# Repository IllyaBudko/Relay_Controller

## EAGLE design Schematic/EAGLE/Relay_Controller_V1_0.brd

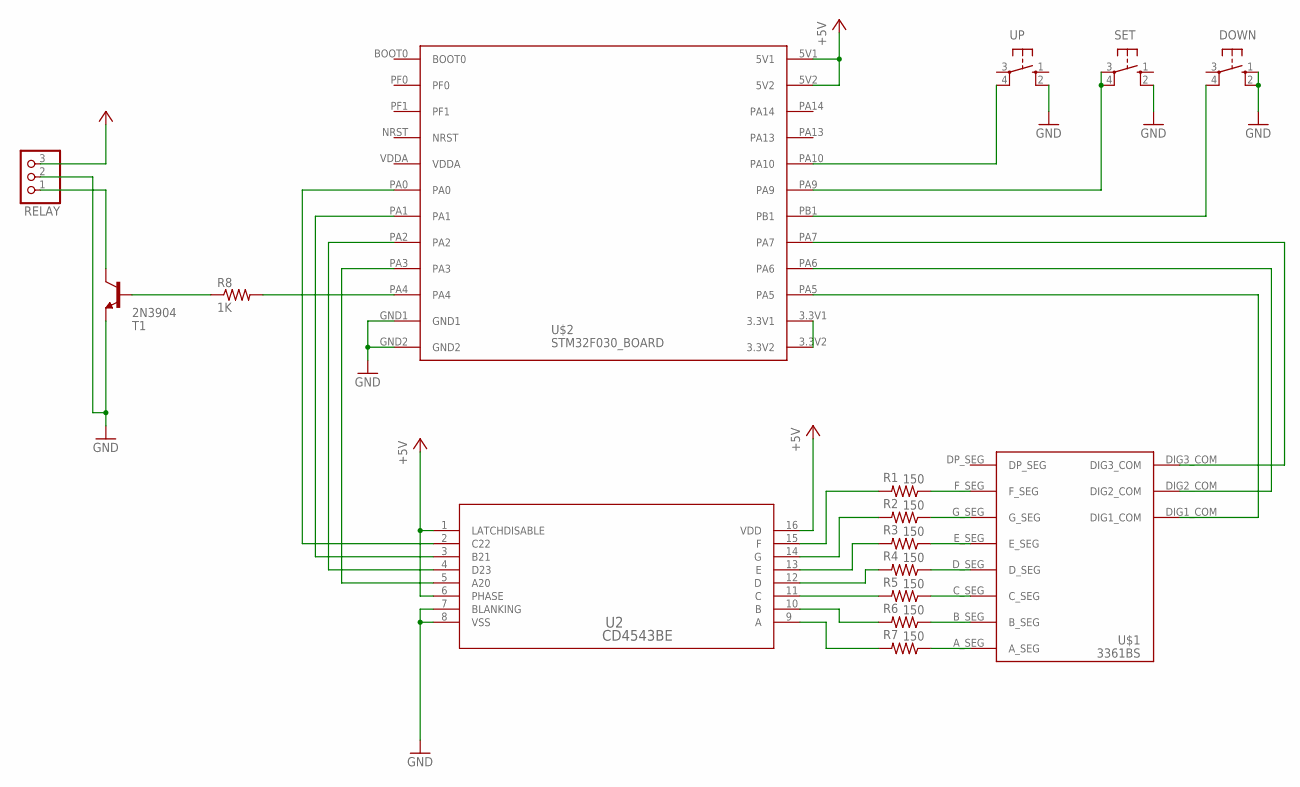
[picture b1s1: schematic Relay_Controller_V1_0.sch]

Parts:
DOWN: 10-XX; B3F-10XX
R1, R2, R3, R4, R5, R6, R7: 150; 0207/7
R8: 1K; 0207/7
RELAY: PINHD-1X3; 1X03
SET: 10-XX; B3F-10XX
T1: 2N3904; TO92
U2: CD4543BE; N16
U$1: 3361BS
U$2: STM32F030_BOARD; STM32F030F4P6_BOARD
UP: 10-XX; B3F-10XX

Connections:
+5V: RELAY.3, U2.1 (LATCHDISABLE), U2.6 (PHASE), U2.16 (VDD), U$2.5V1, U$2.5V2
GND: DOWN.1 (S), DOWN.2 (S1), RELAY.2, SET.2 (S1), T1.3 (E), U2.7 (BLANKING), U2.8 (VSS), U$2.GND1, U$2.GND2, UP.2 (S1)
unnamed: R1.1, U$1.F_SEG
unnamed: R2.1, U$1.G_SEG
unnamed: R3.1, U$1.E_SEG
unnamed: R4.1, U$1.D_SEG
unnamed: R5.1, U$1.C_SEG
unnamed: R6.1, U$1.B_SEG
unnamed: R7.1, U$1.A_SEG
unnamed: R7.2, U2.9 (A)
unnamed: R6.2, U2.10 (B)
unnamed: R5.2, U2.11 (C)
unnamed: R1.2, U2.15 (F)
unnamed: R2.2, U2.14 (G)
unnamed: R3.2, U2.13 (E)
unnamed: R4.2, U2.12 (D)
unnamed: U2.2 (C22), U$2.PA0
unnamed: U2.3 (B21), U$2.PA1
unnamed: U2.4 (D23), U$2.PA2
unnamed: U2.5 (A20), U$2.PA3
unnamed: U$1.DIG1_COM, U$2.PA5
unnamed: U$1.DIG2_COM, U$2.PA6
unnamed: U$1.DIG3_COM, U$2.PA7
unnamed: U$2.3.3V1, U$2.3.3V2
unnamed: DOWN.4 (P1), U$2.PB1
unnamed: R8.2, U$2.PA4
unnamed: U$2.PA10, UP.4 (P1)
unnamed: RELAY.1, T1.1 (C)
unnamed: SET.3, SET.4 (P1), U$2.PA9
unnamed: R8.1, T1.2 (B)

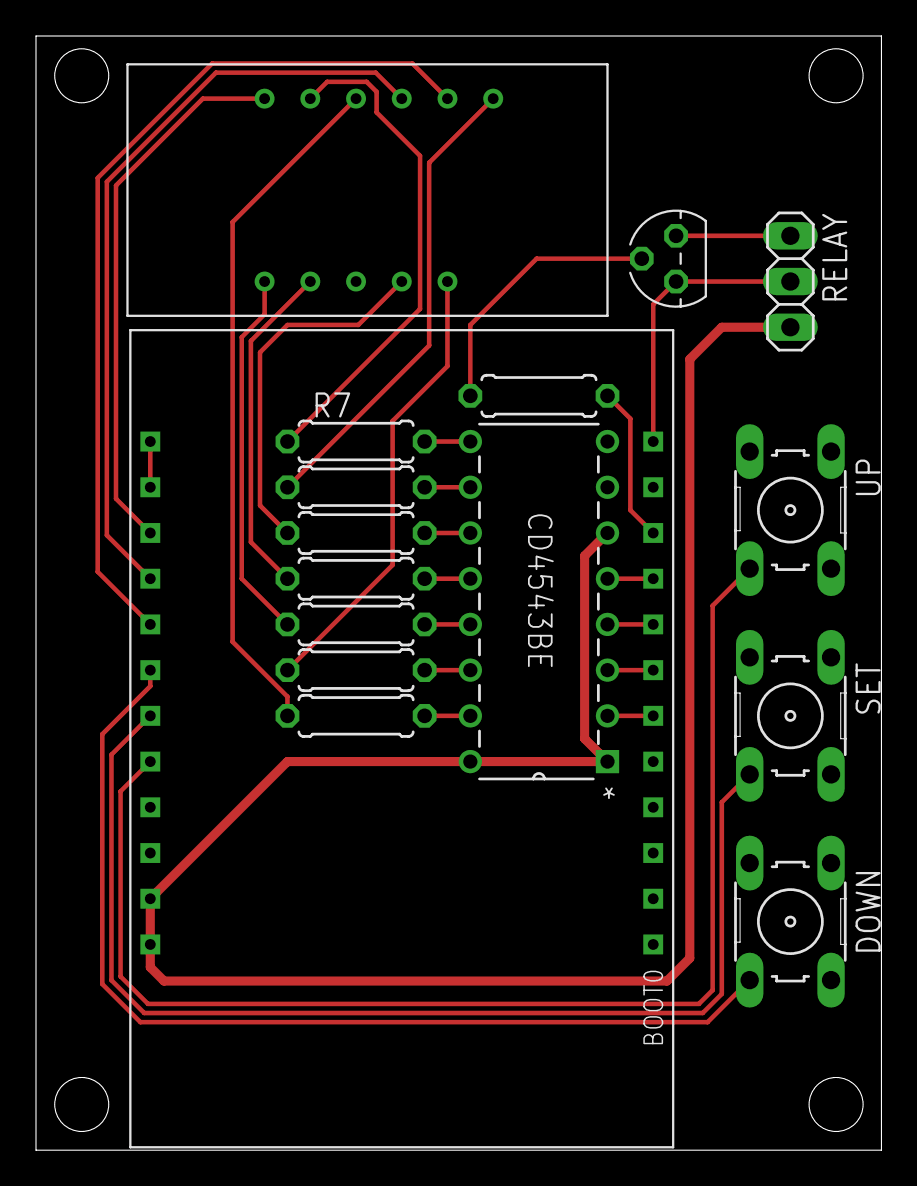
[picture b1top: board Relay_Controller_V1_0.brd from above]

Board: 2 copper layers, 47.0 x 61.9 mm, 16 parts (0 on the bottom side), 30 nets.

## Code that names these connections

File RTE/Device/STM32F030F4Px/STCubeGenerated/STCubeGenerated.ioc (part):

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Mcu.Name=STM32F030F4Px
Mcu.Package=TSSOP20
Mcu.UserName=STM32F030F4Px
PA10.GPIOParameters=GPIO_Label
PA10.GPIO_Label=I2C1_SDA_Display
PA10.Mode=I2C
PA10.Signal=I2C1_SDA
PA2.GPIOParameters=GPIO_Label
PA2.GPIO_Label=UART1_TX_Debug
PA2.Mode=Asynchronous
PA2.Signal=USART1_TX
PA3.GPIOParameters=GPIO_Label
PA3.GPIO_Label=UART2_RX_Debug
PA3.Mode=Asynchronous
PA3.Signal=USART1_RX
PA4.Signal=S_TIM14_CH1
PA5.GPIOParameters=GPIO_Label
PA5.GPIO_Label=Down_Arrow_Key
PA5.Signal=GPIO_Input
PA6.GPIOParameters=GPIO_Label
PA6.GPIO_Label=Set_Key
PA6.Signal=GPIO_Input
PA7.GPIOParameters=GPIO_Label
PA7.GPIO_Label=Up_Arrow_Key
PA7.Signal=GPIO_Input
PA9.GPIOParameters=GPIO_Label
PA9.GPIO_Label=I2C1_SCL_Display
PA9.Mode=I2C
PA9.Signal=I2C1_SCL
PB1.GPIOParameters=GPIO_Label
PB1.GPIO_Label=Relay_Output
PB1.Signal=GPIO_Output
board=custom

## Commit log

2021-04-11 Initial commit on master branch
    - Clean project, with project configs
2021-04-11 Initial commit on develop branch
2021-04-18 works
2021-04-18 changed PWM mode to PWM mode 2 for inverted output
2021-04-18 added transistor switch to turn on and off the relay
2021-04-18 added functionality where the display doesnt blank when a button is pressed
2021-04-19 added timeout functionalty for set functionalty
    - if set is not pressed in appropriate time the display
    changes back to previously set value and the logic
    doesnt change duty cycle
    - also the "to set" value on the display is reset to
    previously set value
2021-04-19 bug fix
    - fixed bug where due to button history on reset
    it sets the duty cycle to 10 percent instead of
    0 percent
2021-04-20 bug fix
    - fixed bug where after using down button and
    timing out by not pressing set, the duty cycle breaks
2021-04-21 added better blinking of display, button detection is a bit more slugish, buttons need to go into inerrupt for next version
2021-04-21 increased blinking rate, button slugishness decreased
2021-04-26 Added Eagle schematics and board files and schematic pdf
2021-04-27 added hex file
2021-05-25 Initial commit on branch "develop_v2"
    - Started adding rotary encoder functionality using state machine
2021-05-26 break commit
    - works, but doesnt keep adding values to working_pulse_idx withouth
    set_button press
2021-05-26 same problem as before
2021-05-26 set_value variable causes problems
2021-05-26 the for loops are causing the problem
2021-05-26 definitely the for loops
2021-05-26 Encoder code seems to work, needs more testing
    - Made a range with counter, instead of for loops because
    they were breaking the code, didnt change to_set values
    proly a timing issue, but now resolved :)
2021-05-26 put a couple of comments
2021-05-26 Changes made:
    - Changed blinking timing
    - Changed encoder rotation to match CW up, CCW down
